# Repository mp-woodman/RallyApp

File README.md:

<!--- Cyber Physical Systems
Author: <Max Holzmann>  Date: <2020 11 29> 
Changes by:
<NAME> - <JJJJ MMM DD> - <comment> 

--->
**Cyber Physical Systems**     

Wintersemester 2020/21
***

# Trainingszeitmesssystem für Oldtimer Gleichmäßigkeitsrallyes 

von: Max Holzmann
***
Diese Tutorial Reihe erklärt detailliert die Implementierung eines kleinen Cyber Physical Systems (CPS ). Bei dem CPS handelt es sich um eine Zeitmessanlage welche beim Training für Oldtimer Gleichmäßigkeitsrallyes zum Einsatz kommen kann.

## Ziele und verwendete Technologien

- Messanlage mit Lichtschranke
  - Berechnung der Zeitdifferenz zwischen der nächsten vollen Minute und der Zeit der Durfahrt mit dem Oldtimer durch die Lichtschranke
  - Grundgedanke:
      - Ein Raspberry Pi als RallyMaster und Basis des Systems
      - Mehrere ESP32 als sogenannte RallyESPs in den Oldtimern zur Visualisierung (visuell und akustisch) der Ergebnisse
 
- Verwendete Technologien
  - **4G Mobilfunk** zur globalden Zeitsynchronisation
  - **Wifi Accesspoint** zur lokalen Kommunikation zwischen Rally Master und Rally ESPs
  - **Node Red** als Hauptanwendung zur Technologie Verknüpfung
  - **MQTT** als Netzwerk Übetragungsprotokoll 
  - **NFC** zur RallyESP registrierung beim RallyMaster
  - **MongoDB** als Datenbank für die Messergebnisse
  - **OPC-UA** als Schnittstelle zur Abfrage von RallyMaster Werten
  - **E-Paper** Display zur Darstellung der Ergebnisse am RallyESP

## Vorraussetzungen und erforderliches Equipment

- Hardware
  - RallyMaster
    - 1x RaspberrPi 3 B [shopping link](https://www.reichelt.de/raspberry-pi-3-b-4x-1-2-ghz-1-gb-ram-wlan-bt-raspberry-pi-3-p164977.html)
    - 1x 7" Raspberry Touch Display (optional) [shopping link](https://www.berrybase.de/raspberry-pi-co/raspberry-pi/displays/offizielles-raspberry-pi-7-display-mit-kapazitiven-touchscreen)
    - 2x NFC Board mit PN532 [shopping link](https://www.amazon.de/ICQUANZX-Nahfeldkommunikationsleser-Modul-Kit-Schlüsselkarte-DIY-Smartphone-Android-Handy/dp/B07VT431QZ/)
    - 1x ESP DevKitC [shopping link](https://www.az-delivery.de/products/esp-32-dev-kit-c-v4)
    - 4G Raspberry Pi HAT mit SIM7600E + SIM Karte [shopping link](https://www.berrybase.de/neu/4g/3g/2g/gsm/gprs/gnss-hat-f-252-r-raspberry-pi-eu-version)
    - Lichtschranke
      - Eigenbau Industrie Reflexlichtschranke auf Stativ mit Optokopplerschaltung zu Anbindung an die GPIO Schnittstelle des Raspberry Pi
    - Kosten: ca. 200€

  - pro RallyESP
    - 1x ESP DevKitC [shopping link](https://www.az-delivery.de/products/esp-32-dev-kit-c-v4)
    - 1x NFC Board mit PN532 [shopping link](https://www.amazon.de/ICQUANZX-Nahfeldkommunikationsleser-Modul-Kit-Schlüsselkarte-DIY-Smartphone-Android-Handy/dp/B07VT431QZ/)
    - 1x Waveshare E-paper 2,9" [shopping link](https://www.reichelt.de/entwicklerboards-display-epaper-2-9-schwarz-weiss-debo-epa-2-9-p224224.html?PROVID=2788&gclid=Cj0KCQiA3Y-ABhCnARIsAKYDH7teyiyXLUv2hSxLMj0LDgHyPWUmo8RROVRIxI7MiENsAM64_XhXIlIaAuo1EALw_wcB)
    - Kosten ca 40€

- Verwendete Software und verwendete Tools in diesem Tutorial
  - Entwiklungsumgebung für den ESP32
    - Arduino IDE
      - Version 1.8.13
    - Visual Studio Code 
      - Windows 10 
      - Visual Studio Code (VS Code)
      - VS Code Extention: Espressiv
  - Tools für den Raspberry Pi
    - Putty als SSH Terminal
    - VNC Viewer als remote desktop connection
    - win32DiskImager als OS immager 

## Beschreibung des gesamten Cyber Physical Systems
Mithilfe dieses CPS kann man die Zeitprüfungen von Oldtimerrallyes üben. Ziel einer Zeitprüfung ist es, möglichst genau bei der vorgegebenen Zeit die Lichtschanke mit dem Auto auszulösen. 

Zu Trainigszwecken fährt man nun immer zu einer vollen Minute (DCF77 oder eines vorgegebenen NTP servers) durch die Lichtschranke. Das CPS wertet die Differenz zur vollen Minute in Millisekunden aus und stellt sie dem Fahrer bereit. Das CPS ist so aufgebaut, dass es einen RallyMaster an der Lichtschranke gibt und mehrere RallyESPs in den teilnehmenden Oldtimern.

Der RallyMaster links und ein RallyESP rechts: \
(Prototypen, im nächsten Entwicklungsschritt werden die Bauteile in einem 3D gedruckten Gehäuse untergebracht und um den Akkubetrieb erweitert):

Möchte ein Teilnehmer trainieren, so meldet er sich mit seinem RallyESP via NFC beim RallyMaster an und erhält eine eindeutige Nummer. Anschließend verbindet sich der RallyESP mit dem WLAN welches der RallyMaster aufspannt. Über die WLAN Verbindung erfolgt nun die weitere Kommunikation. 

Fährt der Teilnehmer mit seinem Oldtimer(incl. RallyESP) durch die Lichtschranke,wird ihm über MQTT sein Ergebnis zugespielt.

Wenn mehrere Teilnehmer und somit mehrere RallyESPs registriert sind, weiss der RallyMaster durch die Signalstärke der WLAN-Verbindung, welcher RallyESP gerade die Lichtschranke ausgelöst hat. So wird sichergestellt, dass das Ergebnis beim richtigen Teilnehmer angezeigt wird.

Der detaillierte Ablauf und das Blockdiagramm des CPS kann den folgenden Abbildungen entnommen werden.

## Lösungsschritte

### zwei Wege der Implementierung

1. Schritt für Schritt Anleitung zur Selbstimplementierung
    1. Lektion 01: Grundlegende Einstellungen der Entwicklungsumgebung und aufsetzen des Pi ([link zur Lektion](0010_General_Setup/README.md))
    2. Lektion 02: Raspberry mit dem 4G Netz verbinden ([link zur Lektion](0020_4G_Connection/README.md))
    3. Lektion 03: Konfigurieren des WLAN chips des Raspberry pi als Acesspoint ([link zur Lektion](0030_Wifi_Acess_Point/README.md))
    4. Lektion 04: Node Red installieren ([link zur Lektion](0040_Node_Red/README.md))
    5. Lektion 05: NFC Registrierung ([link zur Lektion](0050_NFC/README.md))
    6. Lektion 06: MQTT Broker einrichten und in Rally Anwendung Integrieren ([link zur Lektion](0060_MQTT/README.md))
    7. Lektion 07: MongoDB einrichten und in Rally Anwendung Integrieren ([link zur Lektion](0070_MongoDB/README.md))
    8. Lektion 08: OPC UA Server einrichten und mit Android APP testen ([link zur Lektion](0080_OPC_UA/README.md))
    9. Lektion 09: E-paper als Visualisierung der Ergebnisse am RallyESP ([link zur Lektion](0090_E-Paper_Display/README.md))
    10. Testen der Funktionen

2. Verwenden der fertigen Programme aus dieser Tutorial Reihe
    1. Lektion 01: Grundlegende Einstellungen der Entwicklungsumgebung (aufsetzen des Pi nicht erforderlich)([link zur Lektion](0010_General_Setup/README.md))
    2. Fertiges Raspberry Pi 3 B Image der Tutorial Reihe aus dem Ordner 0110_Raspberry_Image mithilfe eines Imagers auf die SD Karte des Pi schreiben. Pi booten und ggf. Netzwerkeistellungen anpassen. Details können in den Lektionen der Tutorial Reihe nachgelesen werden.([link zur Lektion](0110_Raspberry_Images\README.md)
    3. RallyESP Programm aus dem Ordner 0100_Rally_ESP_Code in die Arduino IDE Laden, Übersetzen und auf einen ESP32 übertragen und testen.([link zur Lektion](0100_Rally_ESP_Code\README.md))
    4. Testen der Funktionen

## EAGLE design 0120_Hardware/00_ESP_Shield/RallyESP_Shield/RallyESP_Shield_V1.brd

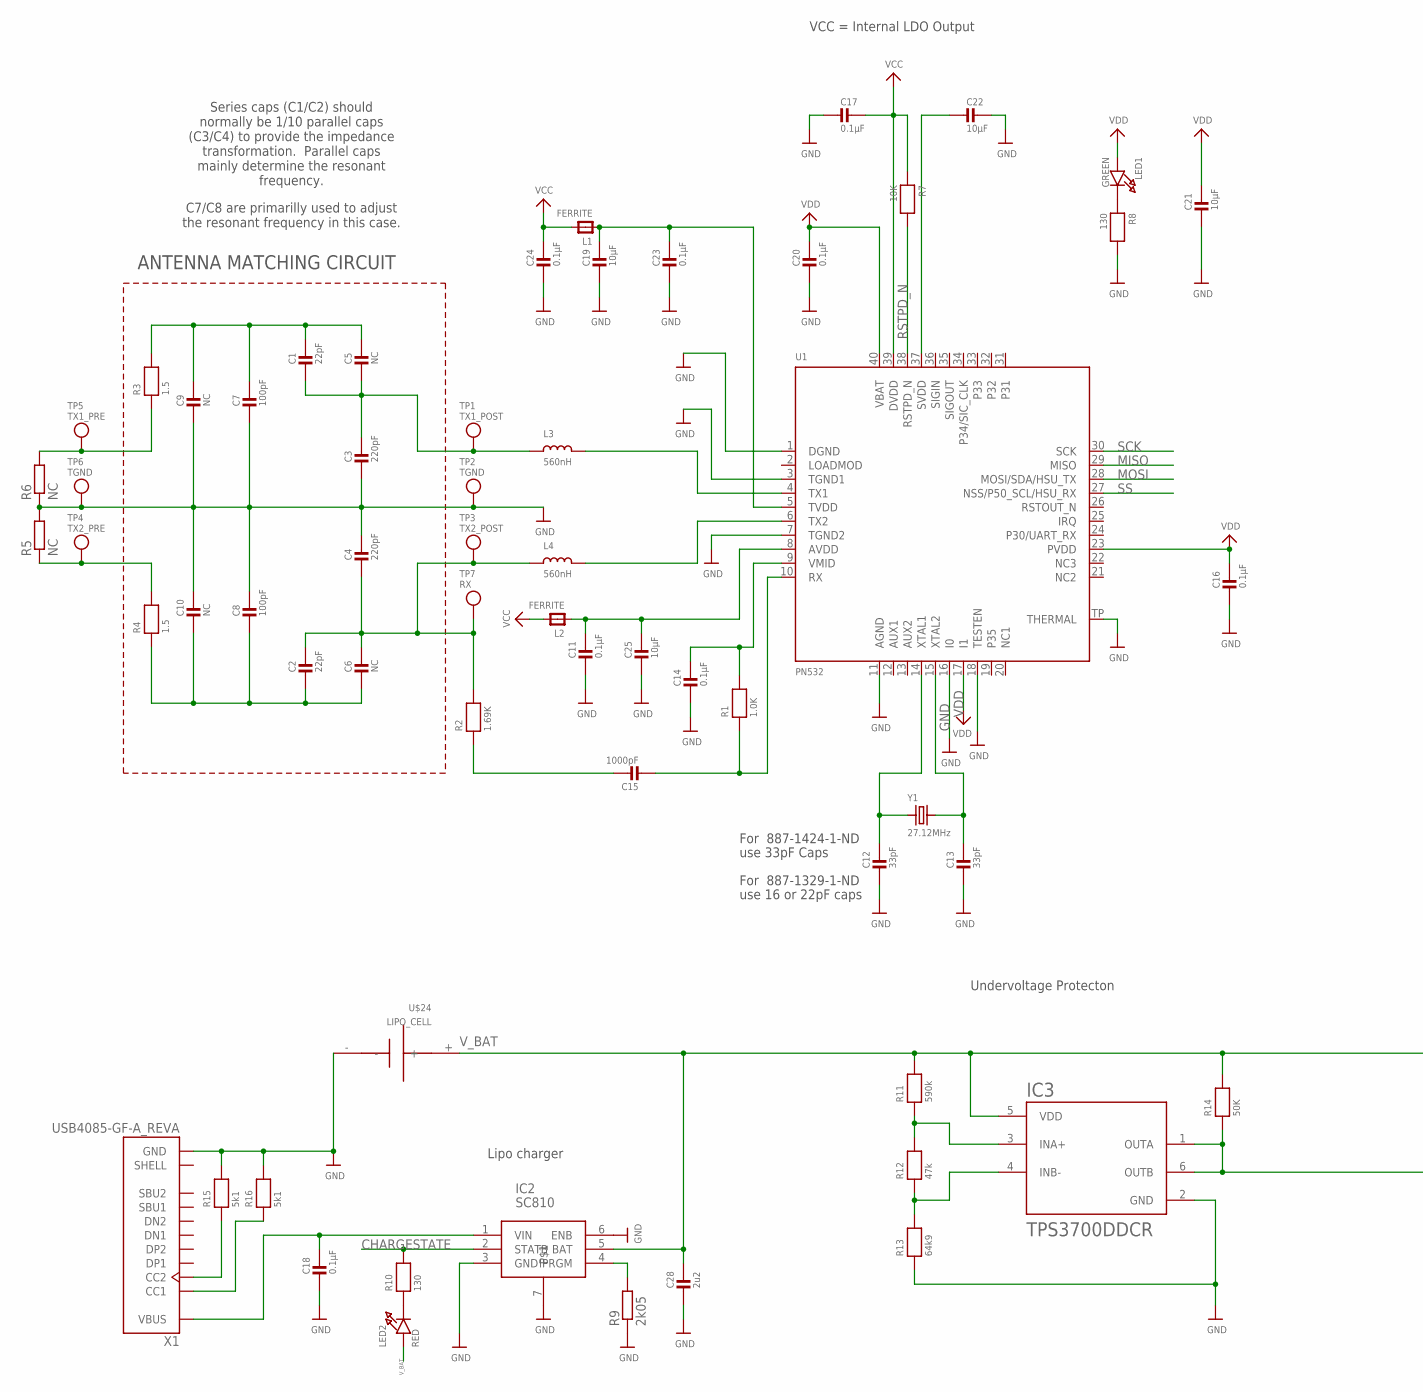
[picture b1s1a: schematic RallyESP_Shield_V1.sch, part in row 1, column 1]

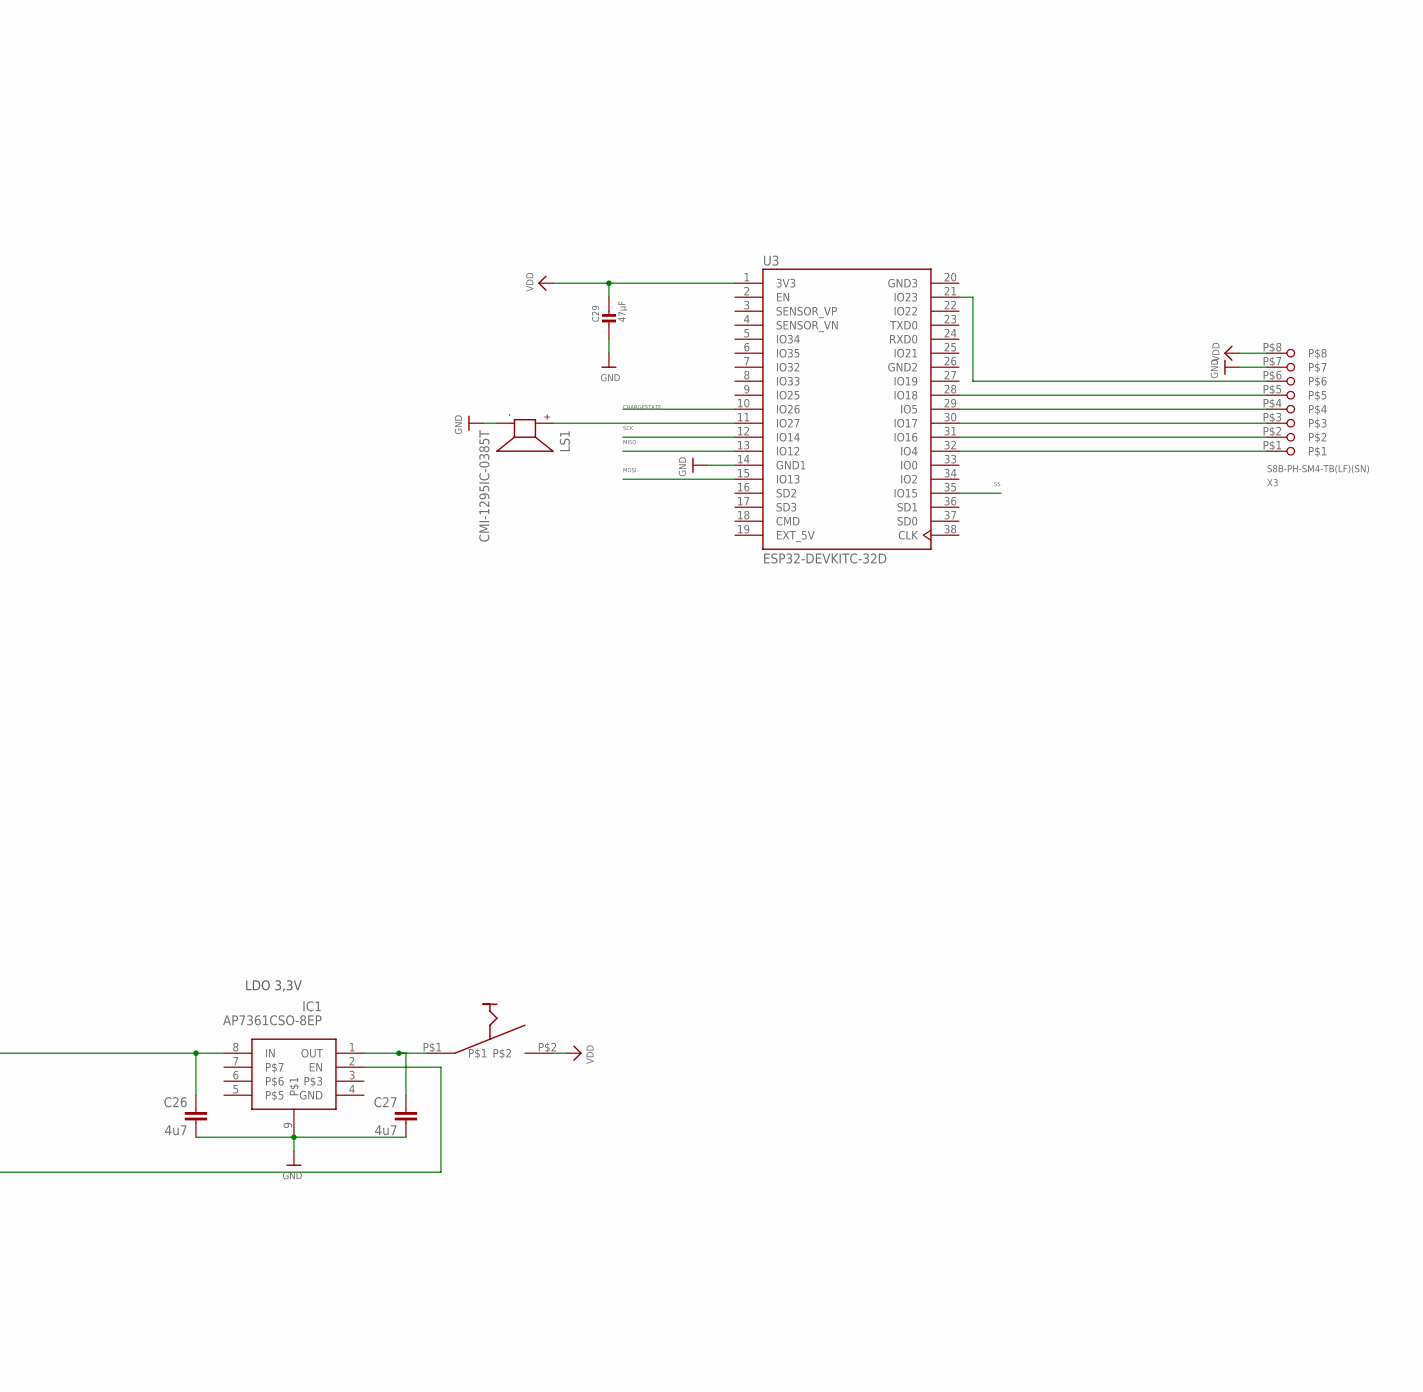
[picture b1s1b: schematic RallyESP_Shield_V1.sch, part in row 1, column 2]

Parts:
C1, C2: 22pF; 0805-NO
C3, C4: 220pF; 0805-NO
C5, C6, C9, C10: NC; 0805-NO
C7, C8: 100pF; 0805-NO
C11, C14, C16, C17, C18, C20, C23, C24: 0.1µF; 0805-NO
C12, C13: 33pF; 0805-NO
C15: 1000pF; 0805-NO
C19, C21, C22, C25: 10µF; 0805-NO
C26, C27: 4u7; C0805
C28: 2u2; 0805-NO
C29: 47µF; 0805-NO
IC1: AP7361CSO-8EP; SOIC127P595X150-9T240X300N
IC2: SC810; MLPD-UT6
IC3: TPS3700DDCR; SOT95P280X110-6N
L1, L2: FERRITE; 0805
L3, L4: 560nH; 0805
LED1: GREEN; CHIPLED_0805_NOOUTLINE
LED2: RED; CHIPLED_0805_NOOUTLINE
LS1: CMI-1295IC-0385T; CUI_CMI-1295IC-0385T
R1: 1.0K; 0805-NO
R2: 1.69K; 0805-NO
R3, R4: 1.5; 0805-NO
R5, R6: NC; R0201
R7: 10K; 0805-NO
R8, R10: 130; 0805-NO
R9: 2k05; R0805
R11: 590k; 0805-NO
R12: 47k; 0805-NO
R13: 64k9; 0805-NO
R14: 50K; 0805-NO
R15, R16: 5k1; 0805-NO
TP1: TX1_POST; TESTPOINT_ROUND_1MM
TP2, TP6: TGND; TESTPOINT_ROUND_1MM
TP3: TX2_POST; TESTPOINT_ROUND_1MM
TP4: TX2_PRE; TESTPOINT_ROUND_1MM
TP5: TX1_PRE; TESTPOINT_ROUND_1MM
TP7: RX; TESTPOINT_ROUND_1MM
U1: PN532; HVQFN40-6X6
U3: ESP32-DEVKITC-32D; MODULE_ESP32-DEVKITC-32D
U$24: LIPO_CELL; LIPO_18X65
U$46: GPTS203211B
X1: USB4085-GF-A_REVA; GCT_USB4085-GF-A_REVA
X3: S8B-PH-SM4-TB(LF)(SN); 8_PIN_SMD_2MM
Y1: 27.12MHz; CRYSTAL_3.2X2.5

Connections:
CHARGESTATE: IC2.2 (STATB), R10.2, U3.10 (IO26)
EXT_5V: U3.19 (EXT_5V)
GND: C3.2, C4.1, C7.2, C8.1, C9.2, C10.1, C11.2, C12.2, C13.2, C14.2, C16.2, C17.2, C18.2, C19.2, C20.2, C21.2, C22.1, C23.2, C24.2, C25.2, C26.2, C27.2, C28.2, C29.2, IC1.9, IC2.3 (GND), IC2.6 (ENB), IC2.7, IC3.2 (GND), LS1.N, R5.2, R6.1, R8.2, R9.1, R13.1, R15.2, R16.2, TP2.P$1, TP6.P$1, U1.1 (DGND), U1.3 (TGND1), U1.7 (TGND2), U1.11 (AGND), U1.16 (I0), U1.18 (TESTEN), U1.TP (THERMAL), U3.14 (GND1), U$24.-, X1.A1 (GND), X1.A12 (GND), X1.B1 (GND), X1.B12 (GND), X3.P$7
GND2: U3.26 (GND2)
GND3: U3.20 (GND3)
MISO: U1.29 (MISO), U3.13 (IO12)
MOSI: U1.28 (MOSI/SDA/HSU_TX), U3.15 (IO13)
unnamed: L3.2, U1.4 (TX1)
unnamed: L4.2, U1.6 (TX2)
unnamed: C1.2, C3.1, C5.2, L3.1, TP1.P$1
unnamed: R3.1, R6.2, TP5.P$1
unnamed: R4.2, R5.1, TP4.P$1
unnamed: LED1.C, R8.1
unnamed: C12.1, U1.14 (XTAL1), Y1.1
unnamed: C13.1, U1.15 (XTAL2), Y1.2
unnamed: C15.1, R2.1
unnamed: C14.1, R1.2, U1.9 (VMID)
unnamed: C15.2, R1.1, U1.10 (RX)
unnamed: C2.1, C4.2, C6.1, L4.1, R2.2, TP3.P$1, TP7.P$1
unnamed: C11.1, C25.1, L2.1, U1.8 (AVDD)
unnamed: C19.1, C23.1, L1.1, U1.5 (TVDD)
unnamed: C22.2, U1.37 (SVDD)
unnamed: LS1.P, U3.11 (IO27)
unnamed: IC3.3 (INA+), R11.1, R12.2
unnamed: IC3.4 (INB-), R12.1, R13.2
unnamed: IC1.2 (EN), IC3.1 (OUTA), IC3.6 (OUTB), R14.1
unnamed: C27.1, IC1.1 (OUT), U$46.P$1
unnamed: R15.1, X1.B5 (CC2)
unnamed: R16.1, X1.A5 (CC1)
unnamed: U3.32 (IO4), X3.P$1
unnamed: U3.31 (IO16), X3.P$2
unnamed: U3.30 (IO17), X3.P$3
unnamed: U3.29 (IO5), X3.P$4
unnamed: U3.28 (IO18), X3.P$5
unnamed: U3.21 (IO23), X3.P$6
unnamed: IC2.4 (IPRGM), R9.2
unnamed: LED2.C, R10.1
unnamed: C18.1, IC2.1 (VIN), X1.A4 (VBUS), X1.A9 (VBUS), X1.B4 (VBUS), X1.B9 (VBUS)
RSTPD_N: R7.2, U1.38 (RSTPD_N)
SCK: U1.30 (SCK), U3.12 (IO14)
SS: U1.27 (NSS/P50_SCL/HSU_RX), U3.35 (IO15)
TX1_ANTENNA: C1.1, C5.1, C7.1, C9.1, R3.2
TX2_ANTENNA: C2.2, C6.2, C8.2, C10.2, R4.1
VCC: C17.1, C24.1, L1.2, L2.2, R7.1, U1.39 (DVDD)
VDD: C16.1, C20.1, C21.1, C29.1, LED1.A, U1.17 (I1), U1.23 (PVDD), U1.40 (VBAT), U3.1 (3V3), U$46.P$2, X3.P$8
V_BAT: C26.1, C28.1, IC1.8 (IN), IC2.5 (BAT), IC3.5 (VDD), LED2.A, R11.2, R14.2, U$24.+

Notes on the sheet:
ANTENNA MATCHING CIRCUIT
For 887-1329-1-ND
use 16 or 22pF caps
For 887-1424-1-ND
use 33pF Caps
VCC = Internal LDO Output
Series caps (C1/C2) should normally be 1/10 parallel caps (C3/C4) to provide the impedance transformation. Parallel caps mainly determine the resonant frequency.
C7/C8 are primarilly used to adjust the resonant frequency in this case.
Undervoltage Protecton
Lipo charger
LDO 3,3V

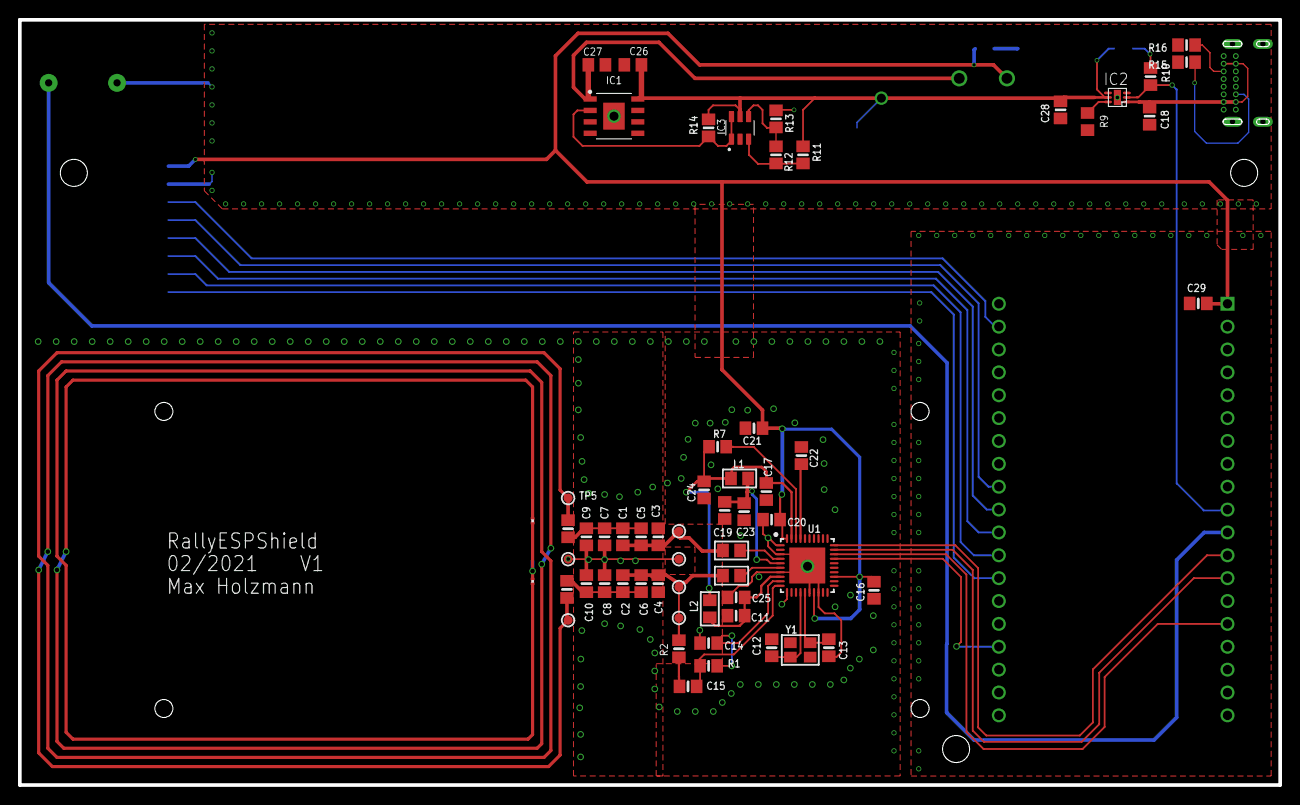
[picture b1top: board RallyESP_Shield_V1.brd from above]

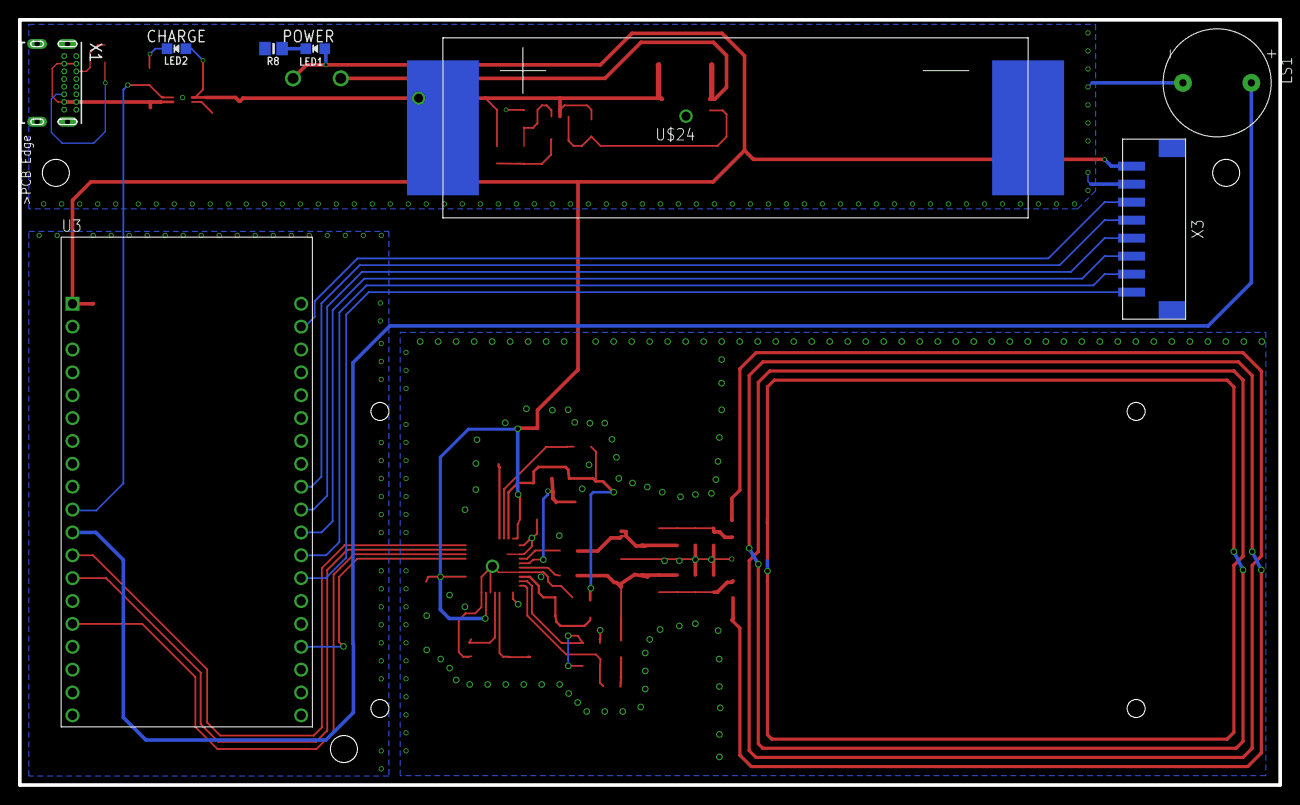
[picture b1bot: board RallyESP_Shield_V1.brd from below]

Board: 2 copper layers, 140.0 x 85.0 mm, 69 parts (8 on the bottom side), 43 nets.

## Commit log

2021-01-18 GITIGNORE und GITATTRIBUTES hinzufügen.
2021-01-18 Projektdateien hinzufügen.
2021-01-18 initial RallyApp Commit
2021-01-18 filemane changes
2021-02-15 RallyESPShield PCB added
